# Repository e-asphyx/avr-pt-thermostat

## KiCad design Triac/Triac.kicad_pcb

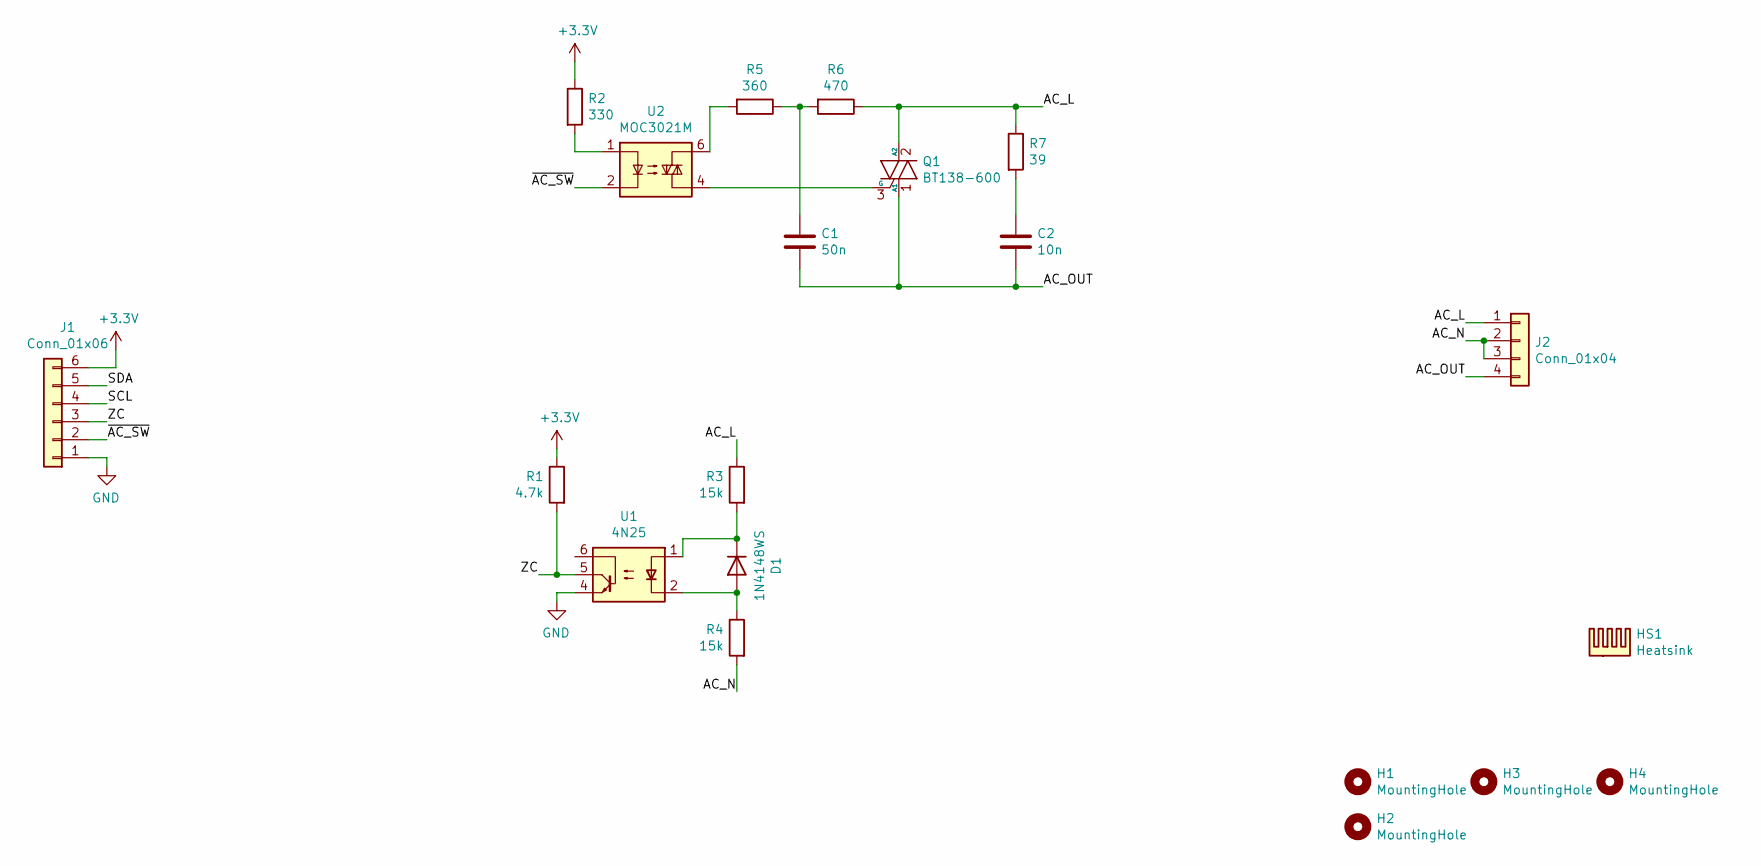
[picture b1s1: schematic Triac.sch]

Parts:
C1: 50n; C_Rect_L18.0mm_W6.0mm_P15.00mm_FKS3_FKP3
C2: 10n; C_Rect_L18.0mm_W6.0mm_P15.00mm_FKS3_FKP3
D1: 1N4148WS; D_SOD-323
H1, H2, H3, H4: MountingHole; MountingHole_3.2mm_M3
HS1: Heatsink; SK64-37.5
J1: Conn_01x06; PinHeader_1x06_P2.54mm_Vertical
J2: Conn_01x04; TerminalBlock_MetzConnect_Type094_RT03504HBLU_1x04_P5.00mm_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
Q1: BT138-600; TO-220-3_Horizontal_TabDown
R1: 4.7k; R_0805_2012Metric
R2: 330; R_0805_2012Metric
R3, R4: 15k; R_2512_6332Metric
R5: 360; R_0805_2012Metric
R6: 470; R_0805_2012Metric
R7: 39; R_0805_2012Metric
U1: 4N25; DIP-6_W7.62mm
U2: MOC3021M; DIP-6_W7.62mm

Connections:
+3V3: J1.6, R1.1, R2.1
/AC_L: J2.1, Q1.2 (A2), R3.1, R6.1, R7.1
/AC_N: J2.2, J2.3, R4.2
/AC_OUT: C1.2, C2.2, J2.4, Q1.1 (A1)
/SCL: J1.4
/SDA: J1.5
/ZC: J1.3, R1.2, U1.5
/~AC_SW: J1.2, U2.2
GND: J1.1, U1.4
unnamed: C1.1, R5.1, R6.2
unnamed: C2.1, R7.2
unnamed: D1.1 (K), R3.2, U1.1
unnamed: D1.2 (A), R4.1, U1.2
unnamed: Q1.3 (G), U2.4
unnamed: R2.2, U2.1
unnamed: R5.2, U2.6

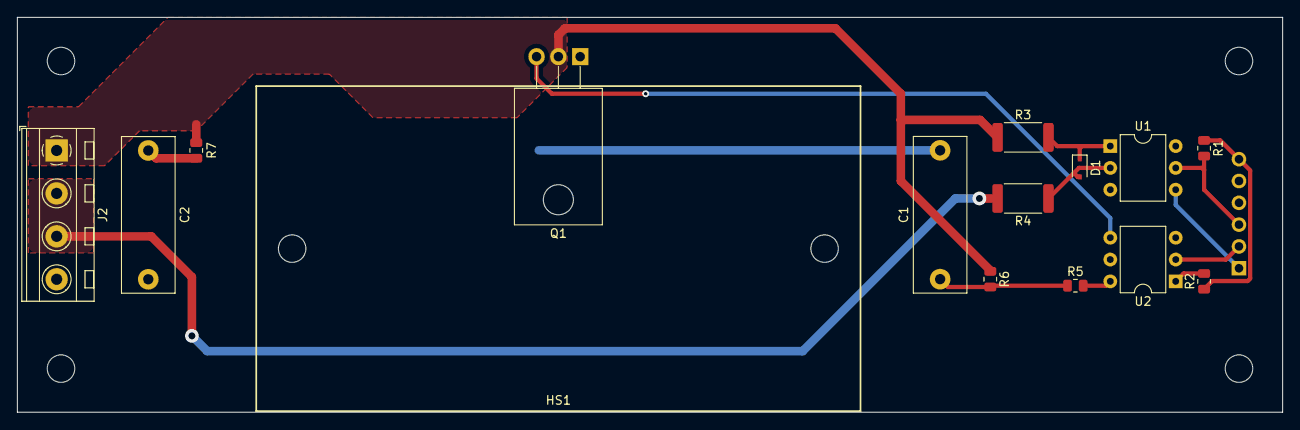
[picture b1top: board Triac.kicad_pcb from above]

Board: 2 copper layers, 147.3 x 46.0 mm, 20 parts (1 on the bottom side), 14 nets.

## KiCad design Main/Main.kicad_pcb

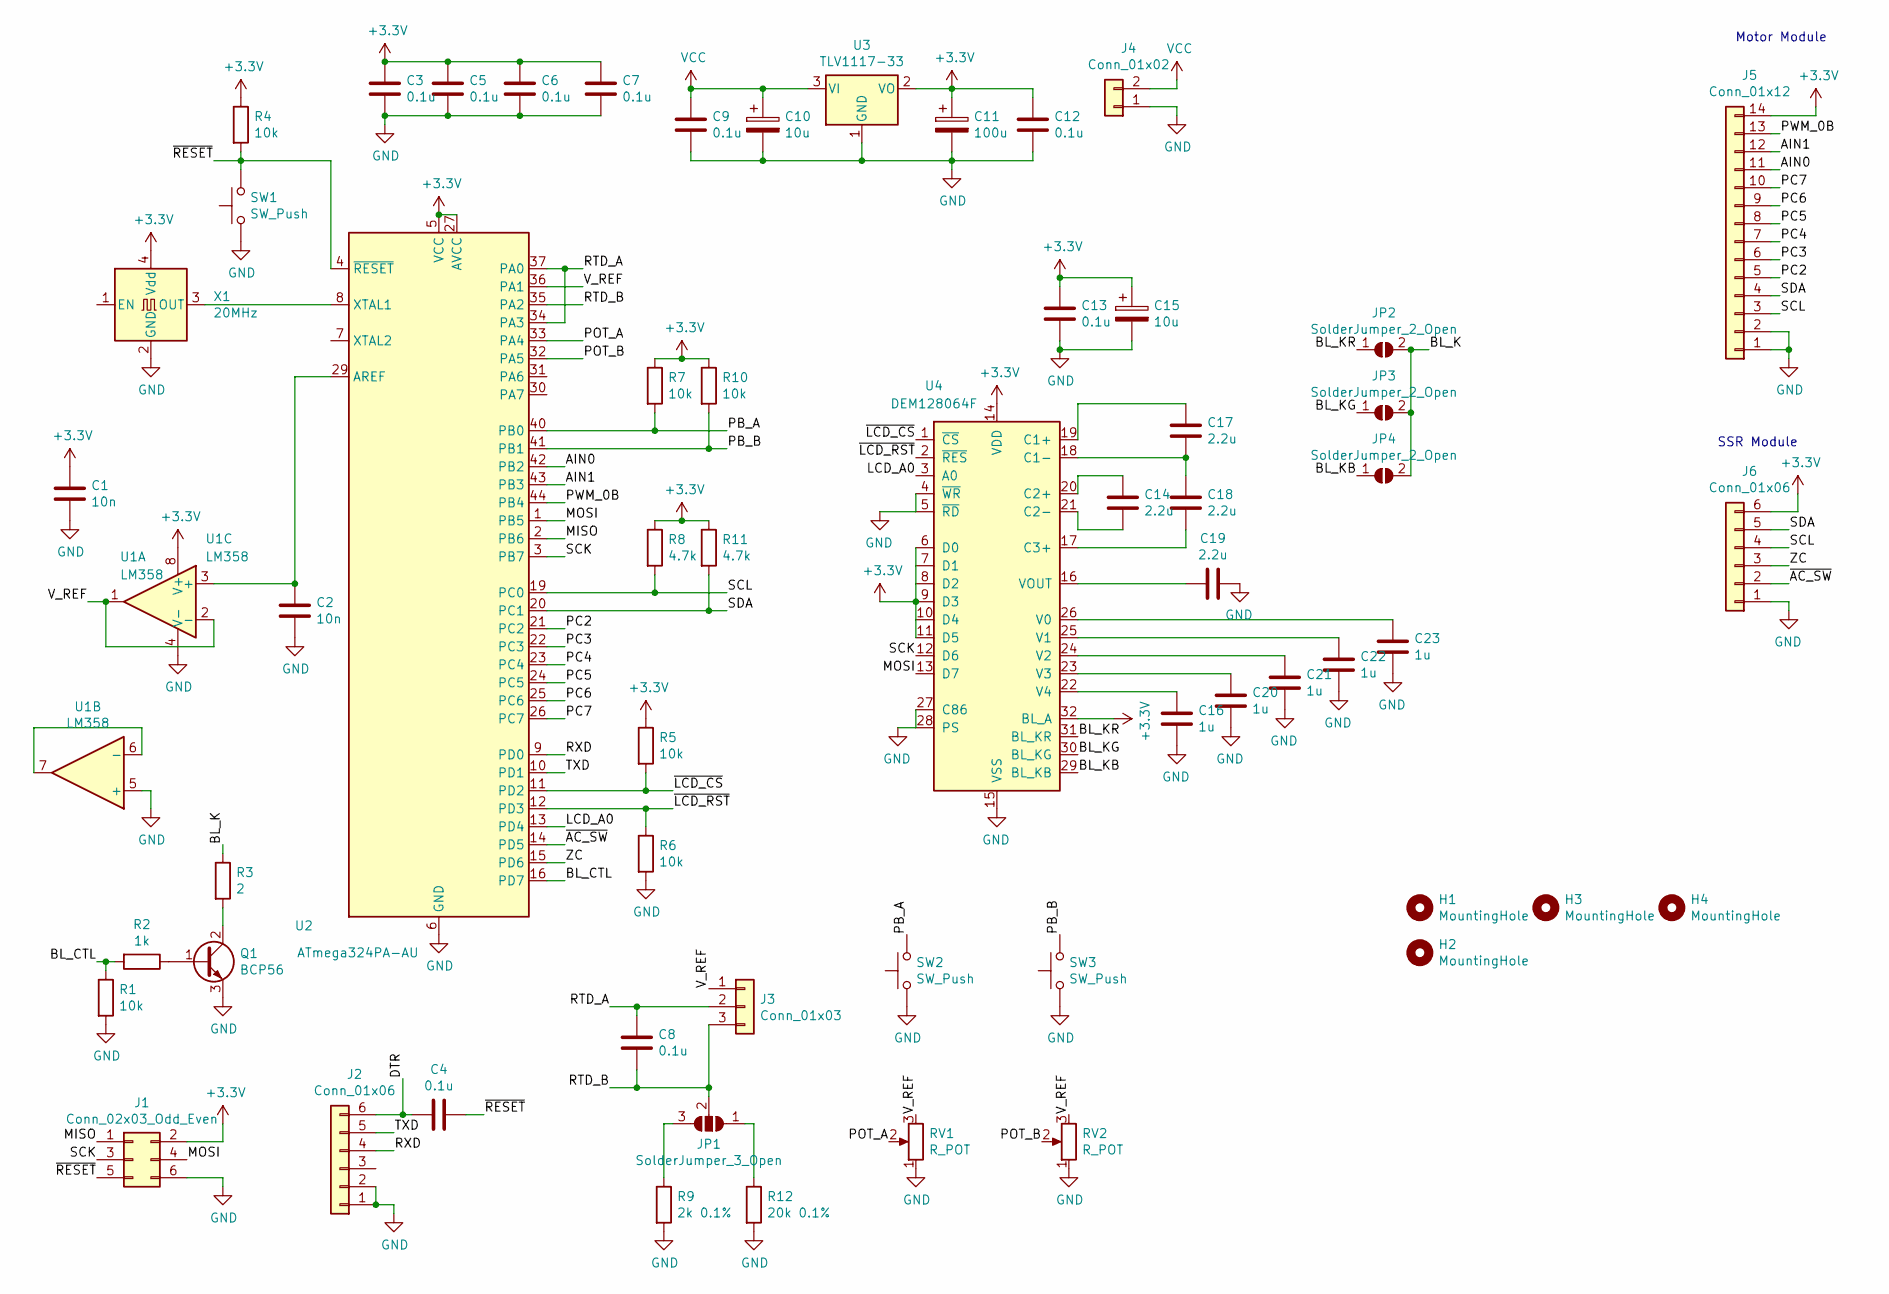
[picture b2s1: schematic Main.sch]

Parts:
C1, C2: 10n; C_0805_2012Metric
C3, C4, C5, C6, C7, C8, C9, C12, C13: 0.1u; C_0805_2012Metric
C10, C15: 10u; CP_Elec_4x5.8
C11: 100u; CP_Elec_5x5.8
C14, C17, C18, C19: 2.2u; C_0805_2012Metric
C16, C20, C21, C22, C23: 1u; C_0805_2012Metric
H1, H2, H3, H4: MountingHole; MountingHole_3.2mm_M3
J1: Conn_02x03_Odd_Even; IDC-Header_2x03_P2.54mm_Vertical
J2: Conn_01x06; PinHeader_1x06_P2.54mm_Vertical
J3: Conn_01x03; TerminalBlock_MetzConnect_Type094_RT03503HBLU_1x03_P5.00mm_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
J4: Conn_01x02; TerminalBlock_MetzConnect_Type094_RT03502HBLU_1x02_P5.00mm_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
J5: Conn_01x12; JST_EH_B14B-EH-A_1x14_P2.50mm_Vertical
J6: Conn_01x06; PinSocket_1x06_P2.54mm_Vertical
JP1: SolderJumper_3_Open; SolderJumper-3_P1.3mm_Open_RoundedPad1.0x1.5mm
JP2, JP3, JP4: SolderJumper_2_Open; SolderJumper-2_P1.3mm_Open_RoundedPad1.0x1.5mm
Q1: BCP56; SOT-223
R1, R4, R5, R6, R7, R10: 10k; R_0805_2012Metric
R2: 1k; R_0805_2012Metric
R3: 2; R_0805_2012Metric
R8, R11: 4.7k; R_0805_2012Metric
R9: 2k 0.1%; R_0805_2012Metric
R12: 20k 0.1%; R_0805_2012Metric
RV1, RV2: R_POT; Potentiometer_Alps_RK09L_Single_Vertical
SW1: SW_Push; SW_SPST_EVQP2
SW2, SW3: SW_Push; SW_Push_1P1T_NO_6x6mm_H9.5mm
U1: LM358; SO-8_3.9x4.9mm_P1.27mm
U2: ATmega324PA-AU; TQFP-44_10x10mm_P0.8mm
U3: TLV1117-33; SOT-223-3_TabPin2
U4: DEM128064F
X1: 20MHz; Oscillator_SMD_Abracon_ASE-4Pin_3.2x2.5mm

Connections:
+3V3: C1.1, C3.1, C5.1, C6.1, C7.1, C11.1, C12.1, C13.1, C15.1, J1.2, J5.14, J6.6, R4.1, R5.1, R7.1, R8.1, R10.1, R11.1, U1.8 (V+), U2.5 (VCC), U2.17 (VCC), U2.27 (AVCC), U2.38 (VCC), U3.2 (VO), U4.6 (D0), U4.9 (D3), U4.11 (D5), U4.14 (VDD), U4.32 (BL_A), X1.4 (Vdd)
/AIN0: J5.11, U2.42 (PB2)
/AIN1: J5.12, U2.43 (PB3)
/BL_CTL: R1.1, R2.2, U2.16 (PD7)
/BL_K: JP2.2 (B), JP3.2 (B), JP4.2 (B), R3.1
/BL_KB: JP4.1 (A), U4.29 (BL_KB)
/BL_KG: JP3.1 (A), U4.30 (BL_KG)
/BL_KR: JP2.1 (A), U4.31 (BL_KR)
/DTR: C4.2, J2.6
/LCD_A0: U2.13 (PD4), U4.3 (A0)
/MISO: J1.1, U2.2 (PB6)
/MOSI: J1.4, U2.1 (PB5), U4.13 (D7)
/PB_A: R7.2, SW2.2, U2.40 (PB0)
/PB_B: R10.2, SW3.2, U2.41 (PB1)
/PC2: J5.5, U2.21 (PC2)
/PC3: J5.6, U2.22 (PC3)
/PC4: J5.7, U2.23 (PC4)
/PC5: J5.8, U2.24 (PC5)
/PC6: J5.9, U2.25 (PC6)
/PC7: J5.10, U2.26 (PC7)
/POT_A: RV1.2, U2.33 (PA4)
/POT_B: RV2.2, U2.32 (PA5)
/PWM_0B: J5.13, U2.44 (PB4)
/RTD_A: C8.2, J3.2, U2.34 (PA3), U2.37 (PA0)
/RTD_B: C8.1, J3.3, JP1.2 (C), U2.35 (PA2)
/RXD: J2.4, U2.9 (PD0)
/SCK: J1.3, U2.3 (PB7), U4.12 (D6)
/SCL: J5.3, J6.4, R8.2, U2.19 (PC0)
/SDA: J5.4, J6.5, R11.2, U2.20 (PC1)
/TXD: J2.5, U2.10 (PD1)
/V_REF: J3.1, RV1.3, RV2.3, U1.1, U1.2 (-), U2.36 (PA1)
/ZC: J6.3, U2.15 (PD6)
/~AC_SW: J6.2, U2.14 (PD5)
/~LCD_CS: R5.2, U2.11 (PD2), U4.1 (~CS)
/~LCD_RST: R6.1, U2.12 (PD3), U4.2 (~RES)
/~RESET: C4.1, J1.5, R4.2, SW1.2, U2.4 (~RESET)
GND: C1.2, C2.2, C3.2, C5.2, C6.2, C7.2, C9.2, C10.2, C11.2, C12.2, C13.2, C15.2, C16.2, C19.1, C20.2, C21.2, C22.2, C23.2, J1.6, J2.1, J2.2, J4.1, J5.1, J5.2, J6.1, Q1.3 (E), R1.2, R6.2, R9.2, R12.2, RV1.1, RV2.1, SW1.1, SW2.1, SW3.1, U1.4 (V-), U1.5 (+), U2.6 (GND), U2.18 (GND), U2.28 (GND), U2.39 (GND), U3.1 (GND), U4.4 (~WR), U4.5 (~RD), U4.15 (VSS), U4.27 (C86), U4.28 (PS), X1.2 (GND)
unnamed: C2.1, U1.3 (+), U2.29 (AREF)
unnamed: C14.1, U4.20 (C2+)
unnamed: C14.2, U4.21 (C2-)
unnamed: C16.1, U4.22 (V4)
unnamed: C17.1, U4.19 (C1+)
unnamed: C17.2, C18.1, U4.18 (C1-)
unnamed: C18.2, U4.17 (C3+)
unnamed: C19.2, U4.16 (VOUT)
unnamed: C20.1, U4.23 (V3)
unnamed: C21.1, U4.24 (V2)
unnamed: C22.1, U4.25 (V1)
unnamed: C23.1, U4.26 (V0)
unnamed: JP1.1 (A), R12.1
unnamed: JP1.3 (B), R9.1
unnamed: Q1.1 (B), R2.1
unnamed: Q1.2 (C), Q1.4 (C), R3.2
unnamed: U1.6 (-), U1.7
unnamed: U2.8 (XTAL1), X1.3 (OUT)
VCC: C9.1, C10.1, J4.2, U3.3 (VI)

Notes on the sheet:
SSR Module
Motor Module

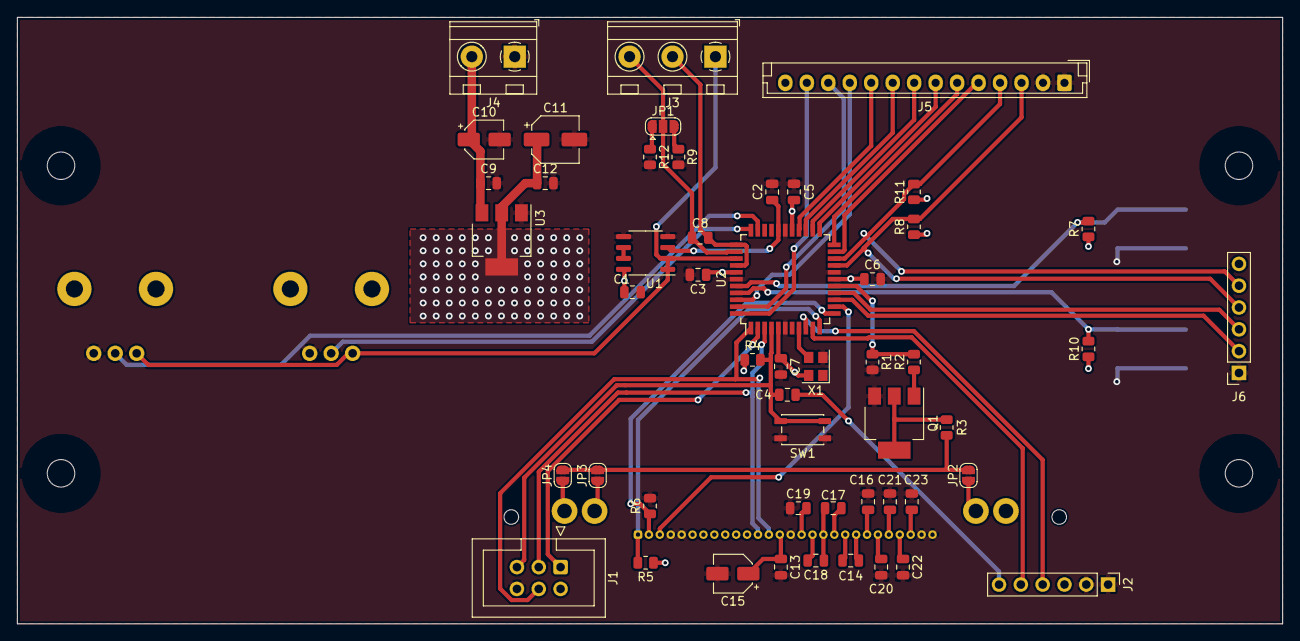
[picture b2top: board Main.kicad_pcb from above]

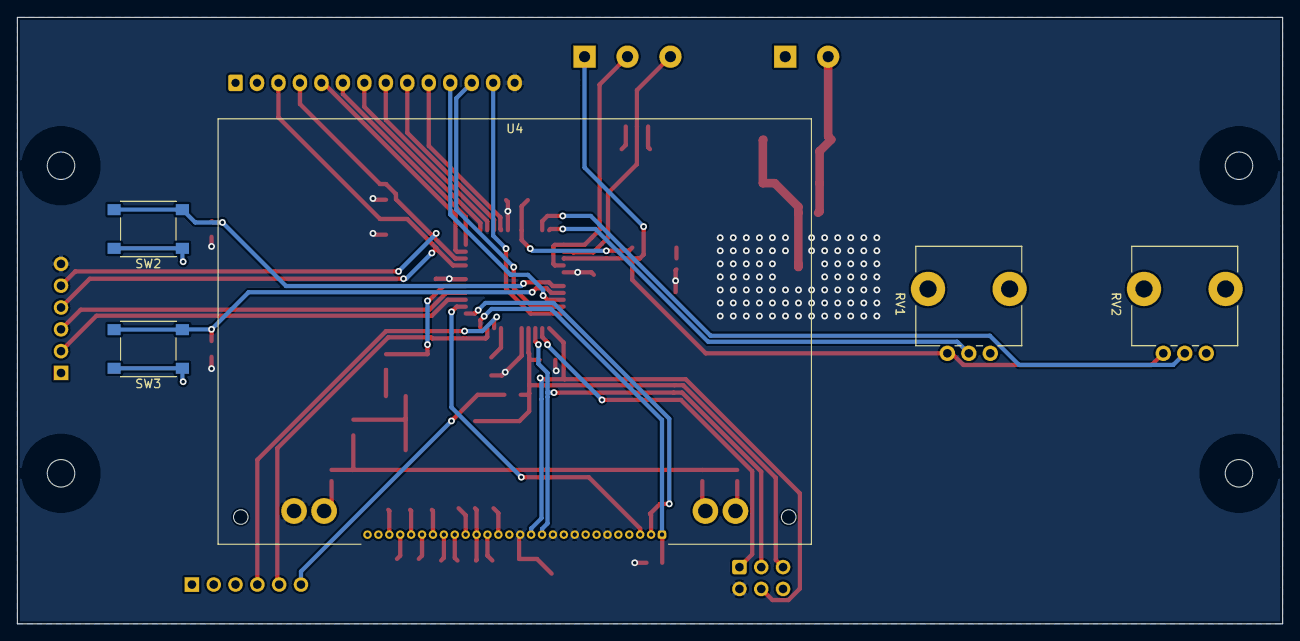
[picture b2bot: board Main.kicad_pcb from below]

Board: 2 copper layers, 147.3 x 70.6 mm, 60 parts (5 on the bottom side), 56 nets.

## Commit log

2021-12-15 Triac board updated
